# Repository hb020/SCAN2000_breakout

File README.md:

# SCAN2000_breakout

This repository contains the KiCAD and Freecad project files for a breakout panel for for a Keithley SCAN2000-20 replacement card.

It is a specific breakout board in the sense that it holds the (solid-state) relays inside, lowering the overal electrical noise.

It is supposed to be matched with the board from [here](https://github.com/hb020/SCAN2000):

either directly, either via a small mezzanine driver/ESD suppression board that can be found in the [/SCAN2000_driver](/SCAN2000_driver) directory.

That latter board will give a bit more protection against small electrical mishaps, and will allow a load of up to 24 or 35mA per pin (depending on the chip manufacturer), instead of 15mA, allowing extra leds to be driven.

To facilitate plugging/unplugging from the DMM, I also made a small 4 pin connector board for the back of the DMM. See the [/SCAN2000_rearconn](/SCAN2000_rearconn) directory.

# Functionality

The board provides 20 channels:

* 2 banana inputs meant for current measurements. It uses 100 mOhm kelvin shunts, allowing up to 2A. One could go higher with lower shunt values or larger package sizes. Note that the accuracy in the µA range suffers from the noise and leak currents in the SSR. This means that if you want a higher current handling capacity, you will sacrifice low current accuracy. And the reverse of course. There are 2 inputs like it, so you are free to adjust, and you can always use external shunts.
* 8 banana inputs for voltage measurements or 4W resistance measurements.
* 10 pin header inputs for voltage measurements or 4W resistance measurements.

# Calibration

See the [/scan2000_calibrate](/scan2000_calibrate) directory for the determination of the multiplication factors for the voltage to current conversion on channels 1 and 11. Can be done simpler though.

A sample TSP file is [here](breakoutAmps.tsp). You may want to add that to your autoexec script.

# Production

The case chosen is a Hammond 1590QBK. It is just small enough to fit everything required inside, and not be a space hogger on my desk. It machines well, even on my rather low end CNC:

The Freecad files, the GCode, as well as the front stickers, are in the [/freecad](/freecad) directory.
The paint on it is not completely flat, making sticker adhesion a bit more difficult and making milled text not practical.

The grounding of the case is done through a threaded rivet in the case that is connected to the ground screw on the rear of the DMM via the shielding of the OUT cable.

# TODO

* Integrate the mezzanine board in the SCAN2000 board. But then I should also replace the ESD diodes by a real overvoltage protection. The used diodes are effective against some types of ESD, but get damaged easily with DC currents. And hand soldering them isn't easy.
* Find a black 26 pin flat cable header, the white one I got now hurts the eyes.
* Use nicer connectors than the MSTB 5.08 connectors. The OUT/SENSE cables that I used to connect to the DMM are shielded, making them just a bit stiff, so I had to use MSTB 2,5/ 2-STZ-5,08 connectors that have strain relief. It would be better to move to a regular 4 or 5 pin connector.
* Make a 3D printed case for the rearconn connector. I just applied plastic coating to the PCB, not ideal.

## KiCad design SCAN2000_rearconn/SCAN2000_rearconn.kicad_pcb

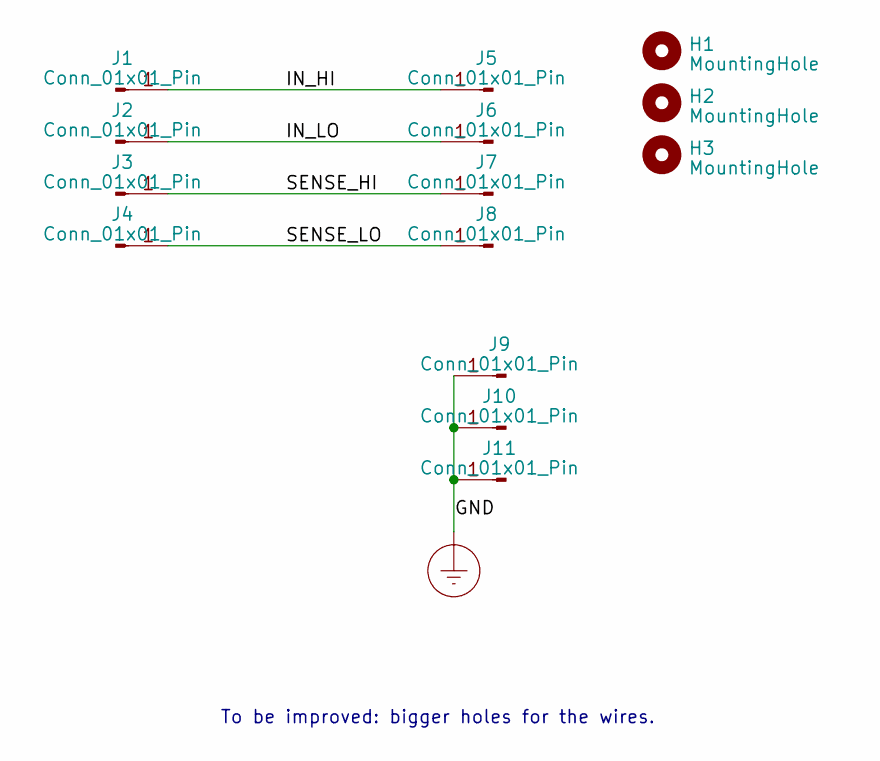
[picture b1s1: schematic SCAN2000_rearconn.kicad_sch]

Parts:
H1, H2, H3: MountingHole; tiewrap_hole
J1, J2, J3, J4: Conn_01x01_Pin; Banana_Jack_1Pin
J5, J6, J7, J8, J9, J10, J11: Conn_01x01_Pin; SolderWire-0.5sqmm_1x01_D0.9mm_OD2.3mm

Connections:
/IN_HI: J1.1, J5.1
/IN_LO: J2.1, J6.1
/SENSE_HI: J3.1, J7.1
/SENSE_LO: J4.1, J8.1
Earth_Protective: J9.1, J10.1, J11.1

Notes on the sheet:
To be improved: bigger holes for the wires.

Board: 2 copper layers, 14 parts (0 on the bottom side), 5 nets, no tracks yet.

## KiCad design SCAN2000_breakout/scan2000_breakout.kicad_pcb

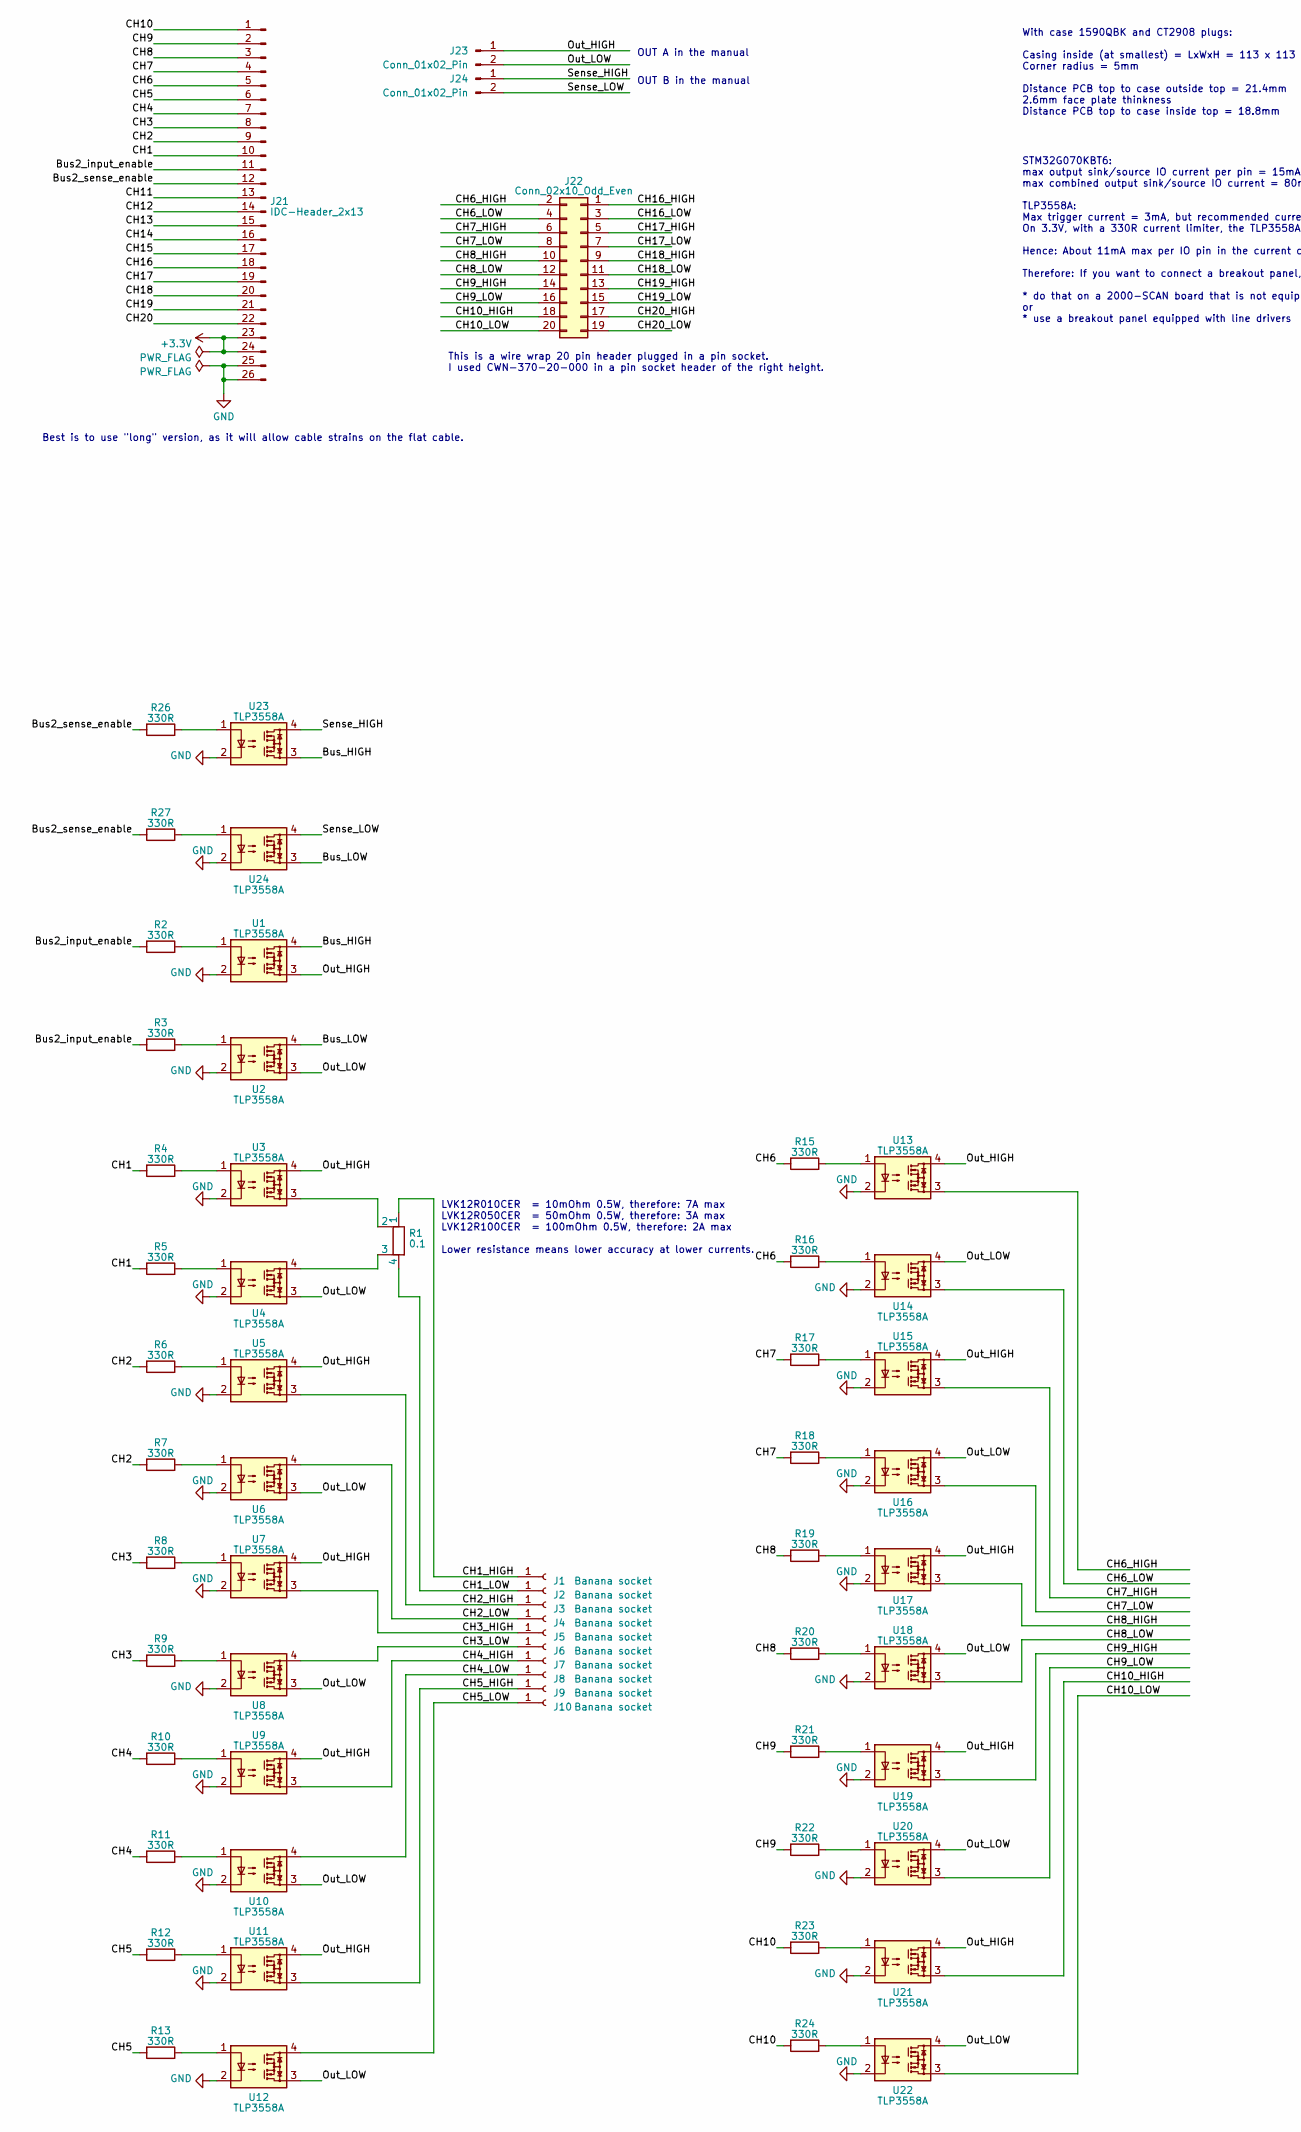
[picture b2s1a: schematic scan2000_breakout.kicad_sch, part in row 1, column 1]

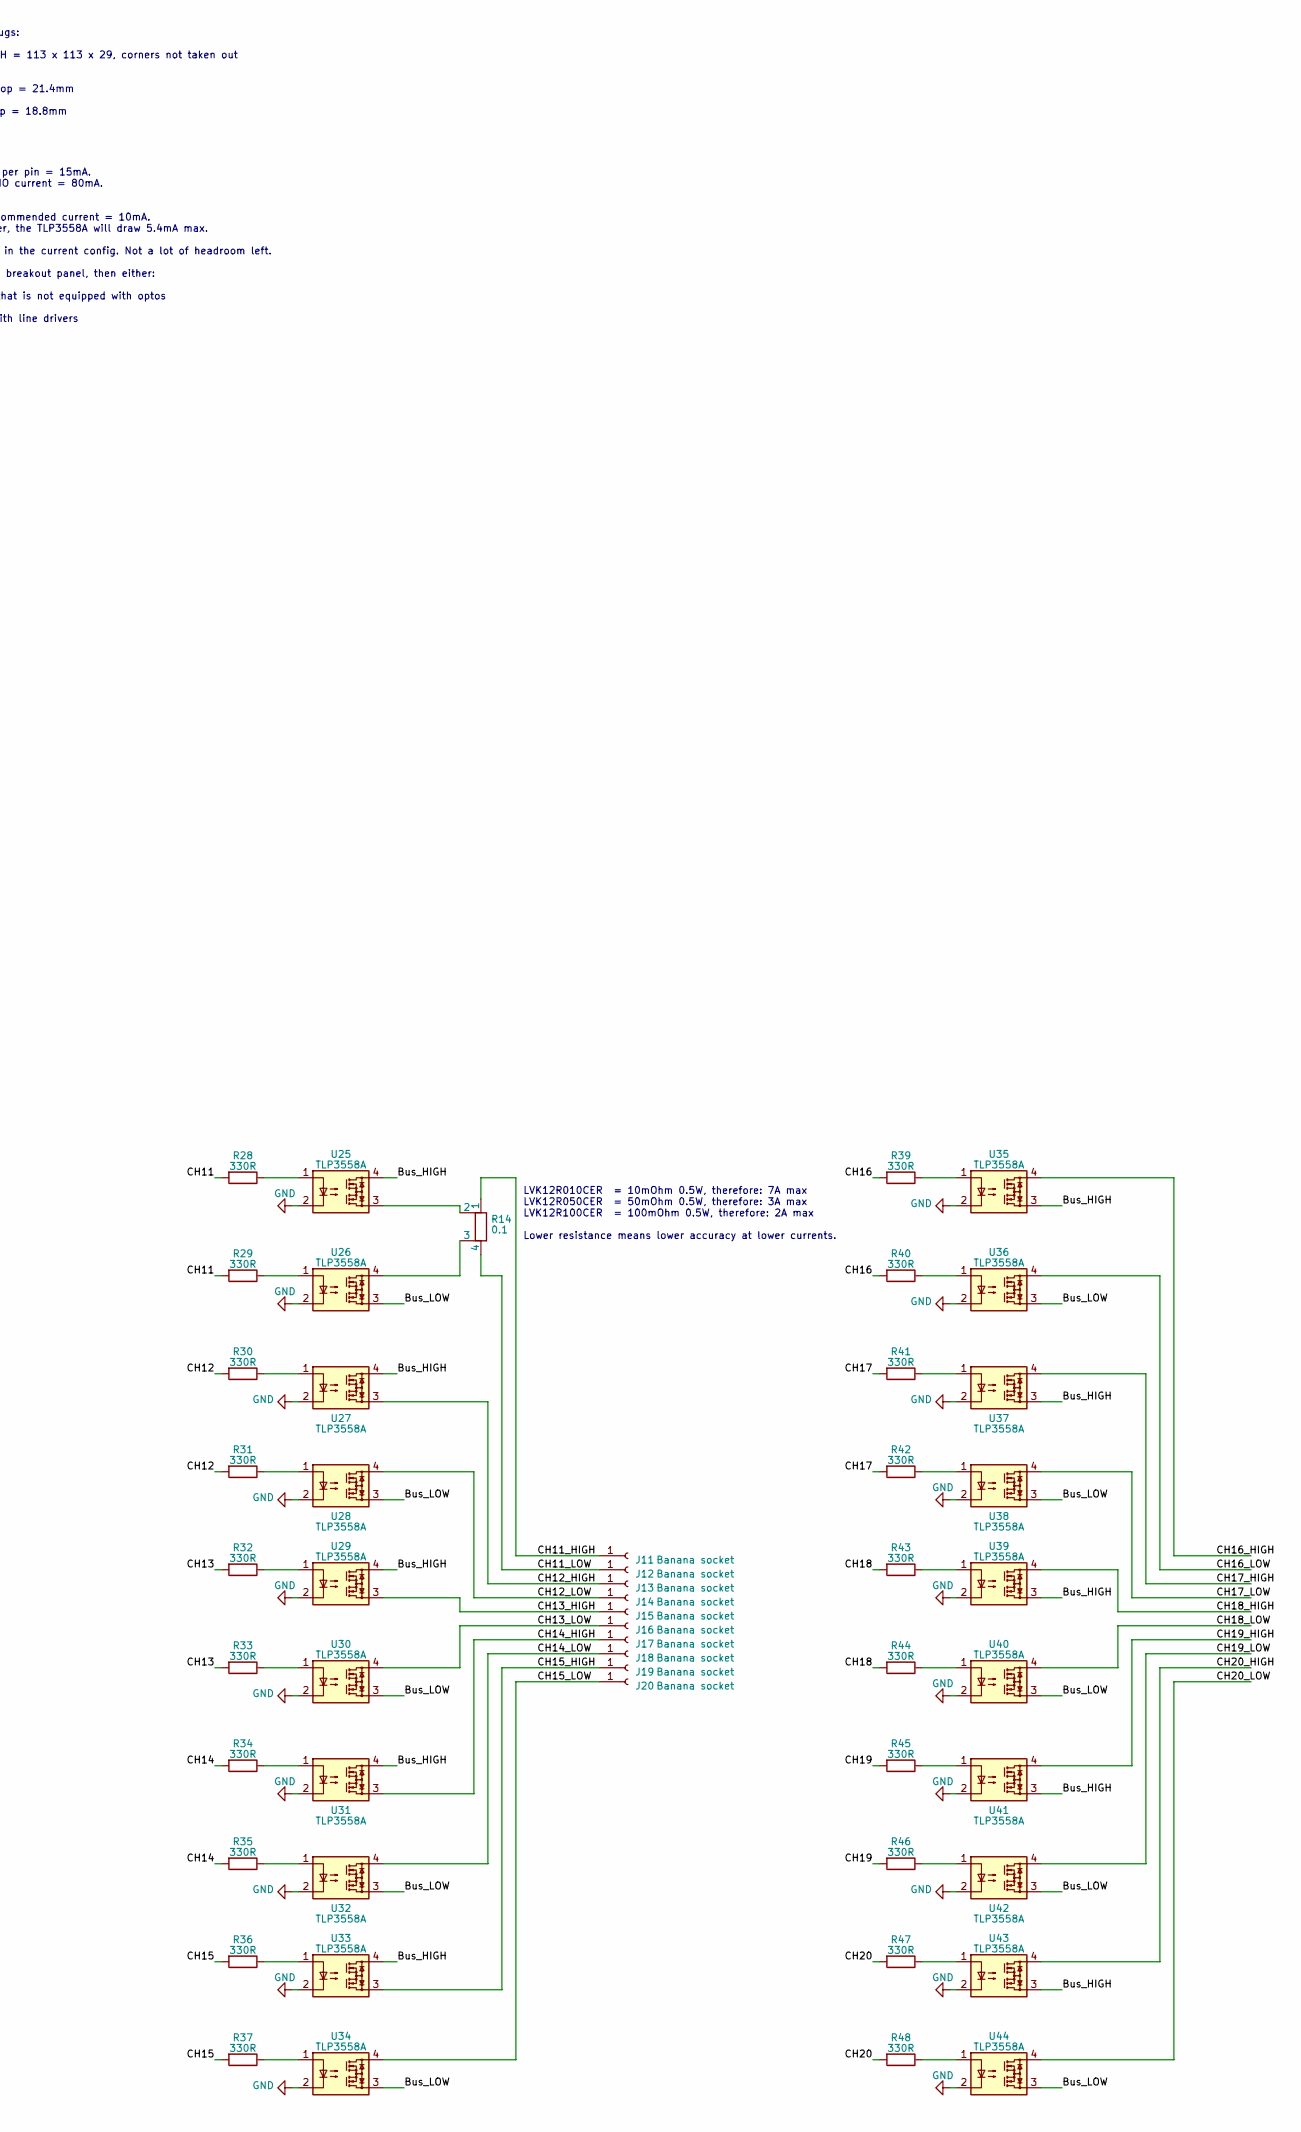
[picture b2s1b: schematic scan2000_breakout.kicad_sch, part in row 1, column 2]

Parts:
J1, J3, J5, J7, J9, J11, J13, J15, J17, J19: Banana socket; CT2908-1
J2, J4, J6, J8, J10, J12, J14, J16, J18, J20: Banana socket; CT2908-0
J21: IDC-Header_2x13; IDC-Header_2x13_P2.54mm_Latch_Horizontal
J22: Conn_02x10_Odd_Even; PinSocket_2x10_P2.54mm_Vertical
J23, J24: Conn_01x02_Pin; PhoenixContact_MSTBA_2,5_2-G-5,08_1x02_P5.08mm_Horizontal
R1, R14: 0.1; R_Shunt_Ohmite_LVK12_ALT2
R2, R3, R4, R5, R6, R7, R8, R9, R10, R11, R12, R13, R15, R16, R17, R18, R19, R20, R21, R22, R23, R24, R26, R27, R28, R29, R30, R31, R32, R33, R34, R35, R36, R37, R39, R40, R41, R42, R43, R44, R45, R46, R47, R48: 330R; R_0603_1608Metric
U1, U2, U3, U4, U5, U6, U7, U8, U9, U10, U11, U12, U13, U14, U15, U16, U17, U18, U19, U20, U21, U22, U23, U24, U25, U26, U27, U28, U29, U30, U31, U32, U33, U34, U35, U36, U37, U38, U39, U40, U41, U42, U43, U44: TLP3558A; DIP-4_W7.62mm

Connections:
+3.3V: J21.23, J21.24
/Bus2_input_enable: J21.11, R2.2, R3.2
/Bus2_sense_enable: J21.12, R26.2, R27.2
/Bus_HIGH: U1.4, U23.3, U25.4, U27.4, U29.4, U31.4, U33.4, U35.3, U37.3, U39.3, U41.3, U43.3
/Bus_LOW: U2.4, U24.3, U26.3, U28.3, U30.3, U32.3, U34.3, U36.3, U38.3, U40.3, U42.3, U44.3
/CH1: J21.10, R4.2, R5.2
/CH1_HIGH: J1.1, R1.1
/CH1_LOW: J2.1, R1.4
/CH2: J21.9, R6.2, R7.2
/CH2_HIGH: J3.1, U5.3
/CH2_LOW: J4.1, U6.4
/CH3: J21.8, R8.2, R9.2
/CH3_HIGH: J5.1, U7.3
/CH3_LOW: J6.1, U8.4
/CH4: J21.7, R10.2, R11.2
/CH4_HIGH: J7.1, U9.3
/CH4_LOW: J8.1, U10.4
/CH5: J21.6, R12.2, R13.2
/CH5_HIGH: J9.1, U11.3
/CH5_LOW: J10.1, U12.4
/CH6: J21.5, R15.2, R16.2
/CH6_HIGH: J22.2, U13.3
/CH6_LOW: J22.4, U14.3
/CH7: J21.4, R17.2, R18.2
/CH7_HIGH: J22.6, U15.3
/CH7_LOW: J22.8, U16.3
/CH8: J21.3, R19.2, R20.2
/CH8_HIGH: J22.10, U17.3
/CH8_LOW: J22.12, U18.3
/CH9: J21.2, R21.2, R22.2
/CH9_HIGH: J22.14, U19.3
/CH9_LOW: J22.16, U20.3
/CH10: J21.1, R23.2, R24.2
/CH10_HIGH: J22.18, U21.3
/CH10_LOW: J22.20, U22.3
/CH11: J21.13, R28.2, R29.2
/CH11_HIGH: J11.1, R14.1
/CH11_LOW: J12.1, R14.4
/CH12: J21.14, R30.2, R31.2
/CH12_HIGH: J13.1, U27.3
/CH12_LOW: J14.1, U28.4
/CH13: J21.15, R32.2, R33.2
/CH13_HIGH: J15.1, U29.3
/CH13_LOW: J16.1, U30.4
/CH14: J21.16, R34.2, R35.2
/CH14_HIGH: J17.1, U31.3
/CH14_LOW: J18.1, U32.4
/CH15: J21.17, R36.2, R37.2
/CH15_HIGH: J19.1, U33.3
/CH15_LOW: J20.1, U34.4
/CH16: J21.18, R39.2, R40.2
/CH16_HIGH: J22.1, U35.4
/CH16_LOW: J22.3, U36.4
/CH17: J21.19, R41.2, R42.2
/CH17_HIGH: J22.5, U37.4
/CH17_LOW: J22.7, U38.4
/CH18: J21.20, R43.2, R44.2
/CH18_HIGH: J22.9, U39.4
/CH18_LOW: J22.11, U40.4
/CH19: J21.21, R45.2, R46.2
/CH19_HIGH: J22.13, U41.4
/CH19_LOW: J22.15, U42.4
/CH20: J21.22, R47.2, R48.2
/CH20_HIGH: J22.17, U43.4
/CH20_LOW: J22.19, U44.4
/Out_HIGH: J23.1, U1.3, U3.4, U5.4, U7.4, U9.4, U11.4, U13.4, U15.4, U17.4, U19.4, U21.4
/Out_LOW: J23.2, U2.3, U4.3, U6.3, U8.3, U10.3, U12.3, U14.4, U16.4, U18.4, U20.4, U22.4
/Sense_HIGH: J24.1, U23.4
/Sense_LOW: J24.2, U24.4
GND: J21.25, J21.26, U1.2, U2.2, U3.2, U4.2, U5.2, U6.2, U7.2, U8.2, U9.2, U10.2, U11.2, U12.2, U13.2, U14.2, U15.2, U16.2, U17.2, U18.2, U19.2, U20.2, U21.2, U22.2, U23.2, U24.2, U25.2, U26.2, U27.2, U28.2, U29.2, U30.2, U31.2, U32.2, U33.2, U34.2, U35.2, U36.2, U37.2, U38.2, U39.2, U40.2, U41.2, U42.2, U43.2, U44.2
unnamed: R1.2, U3.3
unnamed: R1.3, U4.4
unnamed: R2.1, U1.1
unnamed: R3.1, U2.1
unnamed: R4.1, U3.1
unnamed: R5.1, U4.1
unnamed: R6.1, U5.1
unnamed: R7.1, U6.1
unnamed: R8.1, U7.1
unnamed: R9.1, U8.1
unnamed: R10.1, U9.1
unnamed: R11.1, U10.1
unnamed: R12.1, U11.1
unnamed: R13.1, U12.1
unnamed: R14.2, U25.3
unnamed: R14.3, U26.4
unnamed: R15.1, U13.1
unnamed: R16.1, U14.1
unnamed: R17.1, U15.1
unnamed: R18.1, U16.1
unnamed: R19.1, U17.1
unnamed: R20.1, U18.1
unnamed: R21.1, U19.1
unnamed: R22.1, U20.1
unnamed: R23.1, U21.1
unnamed: R24.1, U22.1
unnamed: R26.1, U23.1
unnamed: R27.1, U24.1
unnamed: R28.1, U25.1
unnamed: R29.1, U26.1
unnamed: R30.1, U27.1
unnamed: R31.1, U28.1
unnamed: R32.1, U29.1
unnamed: R33.1, U30.1
unnamed: R34.1, U31.1
unnamed: R35.1, U32.1
unnamed: R36.1, U33.1
unnamed: R37.1, U34.1
unnamed: R39.1, U35.1
unnamed: R40.1, U36.1
unnamed: R41.1, U37.1
unnamed: R42.1, U38.1
unnamed: R43.1, U39.1
unnamed: R44.1, U40.1
unnamed: R45.1, U41.1
unnamed: R46.1, U42.1
unnamed: R47.1, U43.1
unnamed: R48.1, U44.1

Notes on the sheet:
LVK12R010CER = 10mOhm 0.5W, therefore: 7A max LVK12R050CER = 50mOhm 0.5W, therefore: 3A max LVK12R100CER = 100mOhm 0.5W, therefore: 2A max Lower resistance means lower accuracy at lower currents.
Best is to use "long" version, as it will allow cable strains on the flat cable.
OUT B in the manual
STM32G070KBT6: max output sink/source IO current per pin = 15mA. max combined output sink/source IO current = 80mA. TLP3558A: Max trigger current = 3mA, but recommended current = 10mA. On 3.3V, with a 330R current limiter, the TLP3558A will draw 5.4mA max. Hence: About 11mA max per IO pin in the cu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
OUT A in the manual
With case 1590QBK and CT2908 plugs: Casing inside (at smallest) = LxWxH = 113 x 113 x 29, corners not taken out Corner radius = 5mm Distance PCB top to case outside top = 21.4mm 2.6mm face plate thinkness Distance PCB top to case inside top = 18.8mm
This is a wire wrap 20 pin header plugged in a pin socket. I used CWN-370-20-000 in a pin socket header of the right height.

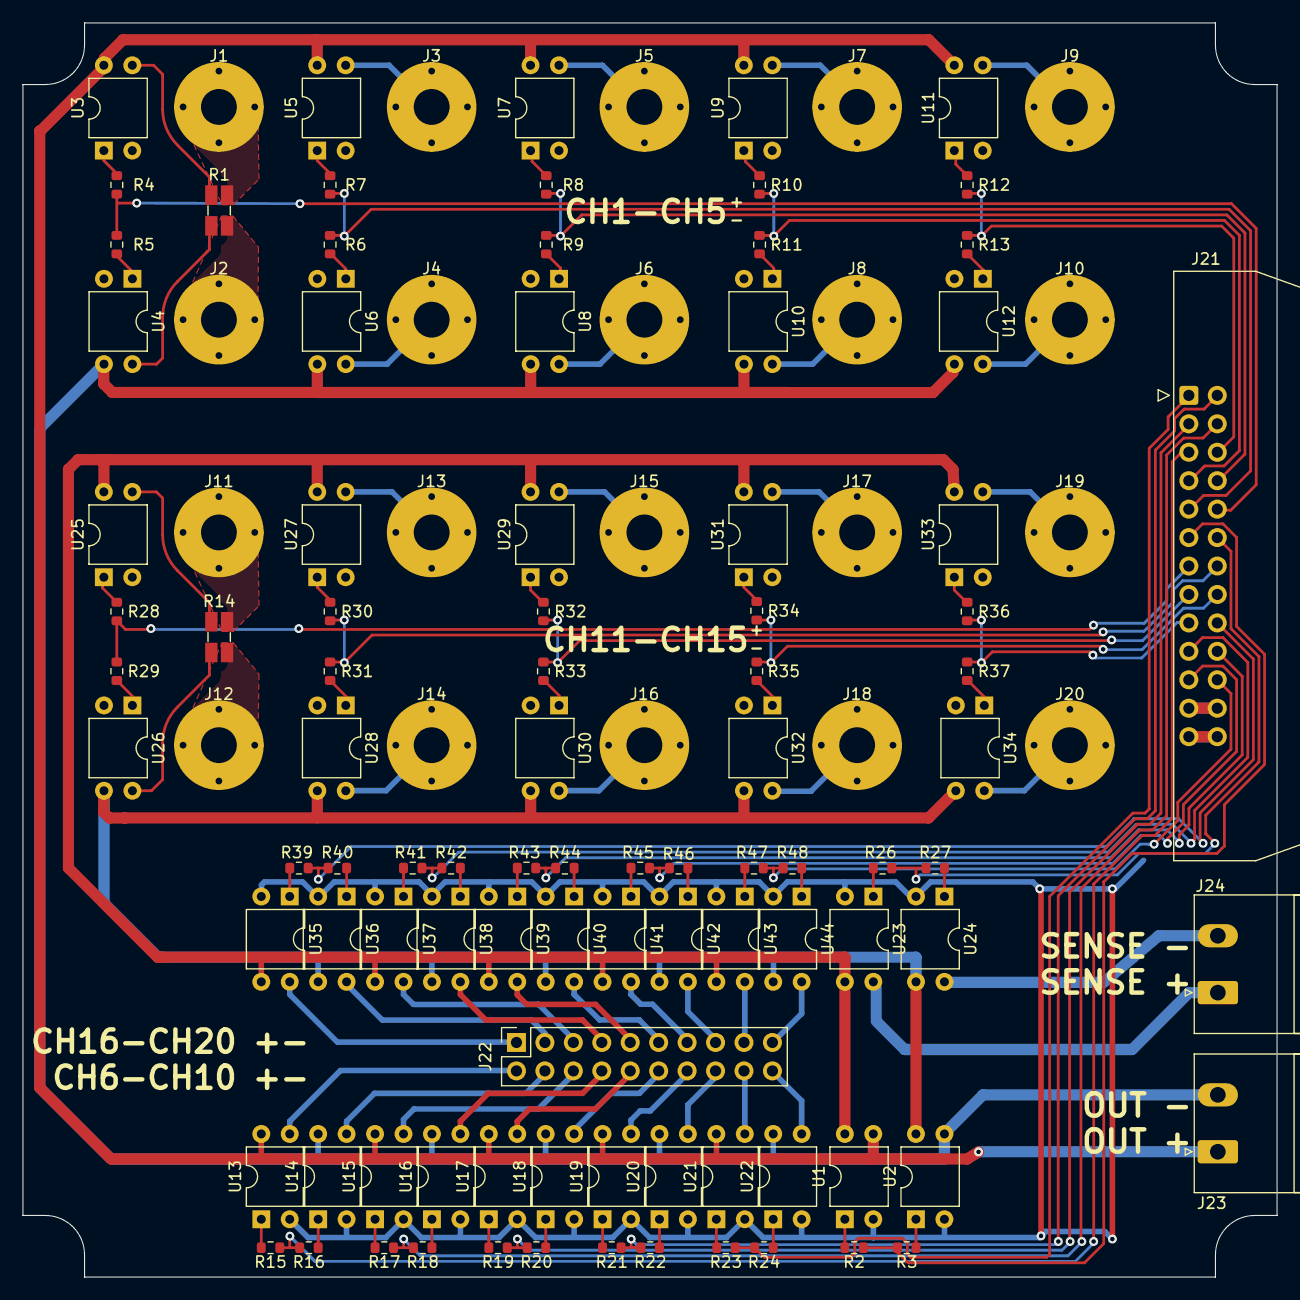
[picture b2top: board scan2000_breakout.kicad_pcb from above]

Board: 2 copper layers, 112.0 x 112.0 mm, 114 parts (0 on the bottom side), 118 nets.

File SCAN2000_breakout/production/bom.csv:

Designator,Footprint,Quantity,Value,LCSC Part #
"J1, J11, J13, J15, J17, J19, J3, J5, J7, J9",CT2908-1,10,Banana socket,
"J10, J12, J14, J16, J18, J2, J20, J4, J6, J8",CT2908-0,10,Banana socket,
J21,IDC-Header_2x13_P2.54mm_Latch_Horizontal,1,Conn_01x26_HIGHin,
J22,PinSocket_2x10_P2.54mm_Vertical,1,Conn_02x10_Odd_Even,
"J23, J24","PhoenixContact_MSTBA_2,5_2-G-5,08_1x02_P5.08mm_Horizontal",2,Conn_01x02_Pin,
"R1, R14",R_Shunt_Ohmite_LVK12_ALT2,2,0.05,
"R10, R11, R12, R13, R15, R16, R17, R18, R19, R2, R20, R21, R22, R23, R24, R26, R27, R28, R29, R3, R30, R31, R32, R33, R34, R35, R36, R37, R39, R4, R40, R41, R42, R43, R44, R45, R46, R47, R48, R5, R6, R7, R8, R9",0603,44,330R,
"U1, U10, U11, U12, U13, U14, U15, U16, U17, U18, U19, U2, U20, U21, U22, U23, U24, U25, U26, U27, U28, U29, U3, U30, U31, U32, U33, U34, U35, U36, U37, U38, U39, U4, U40, U41, U42, U43, U44, U5, U6, U7, U8, U9",DIP-4_W7.62mm,44,TLP3558A,

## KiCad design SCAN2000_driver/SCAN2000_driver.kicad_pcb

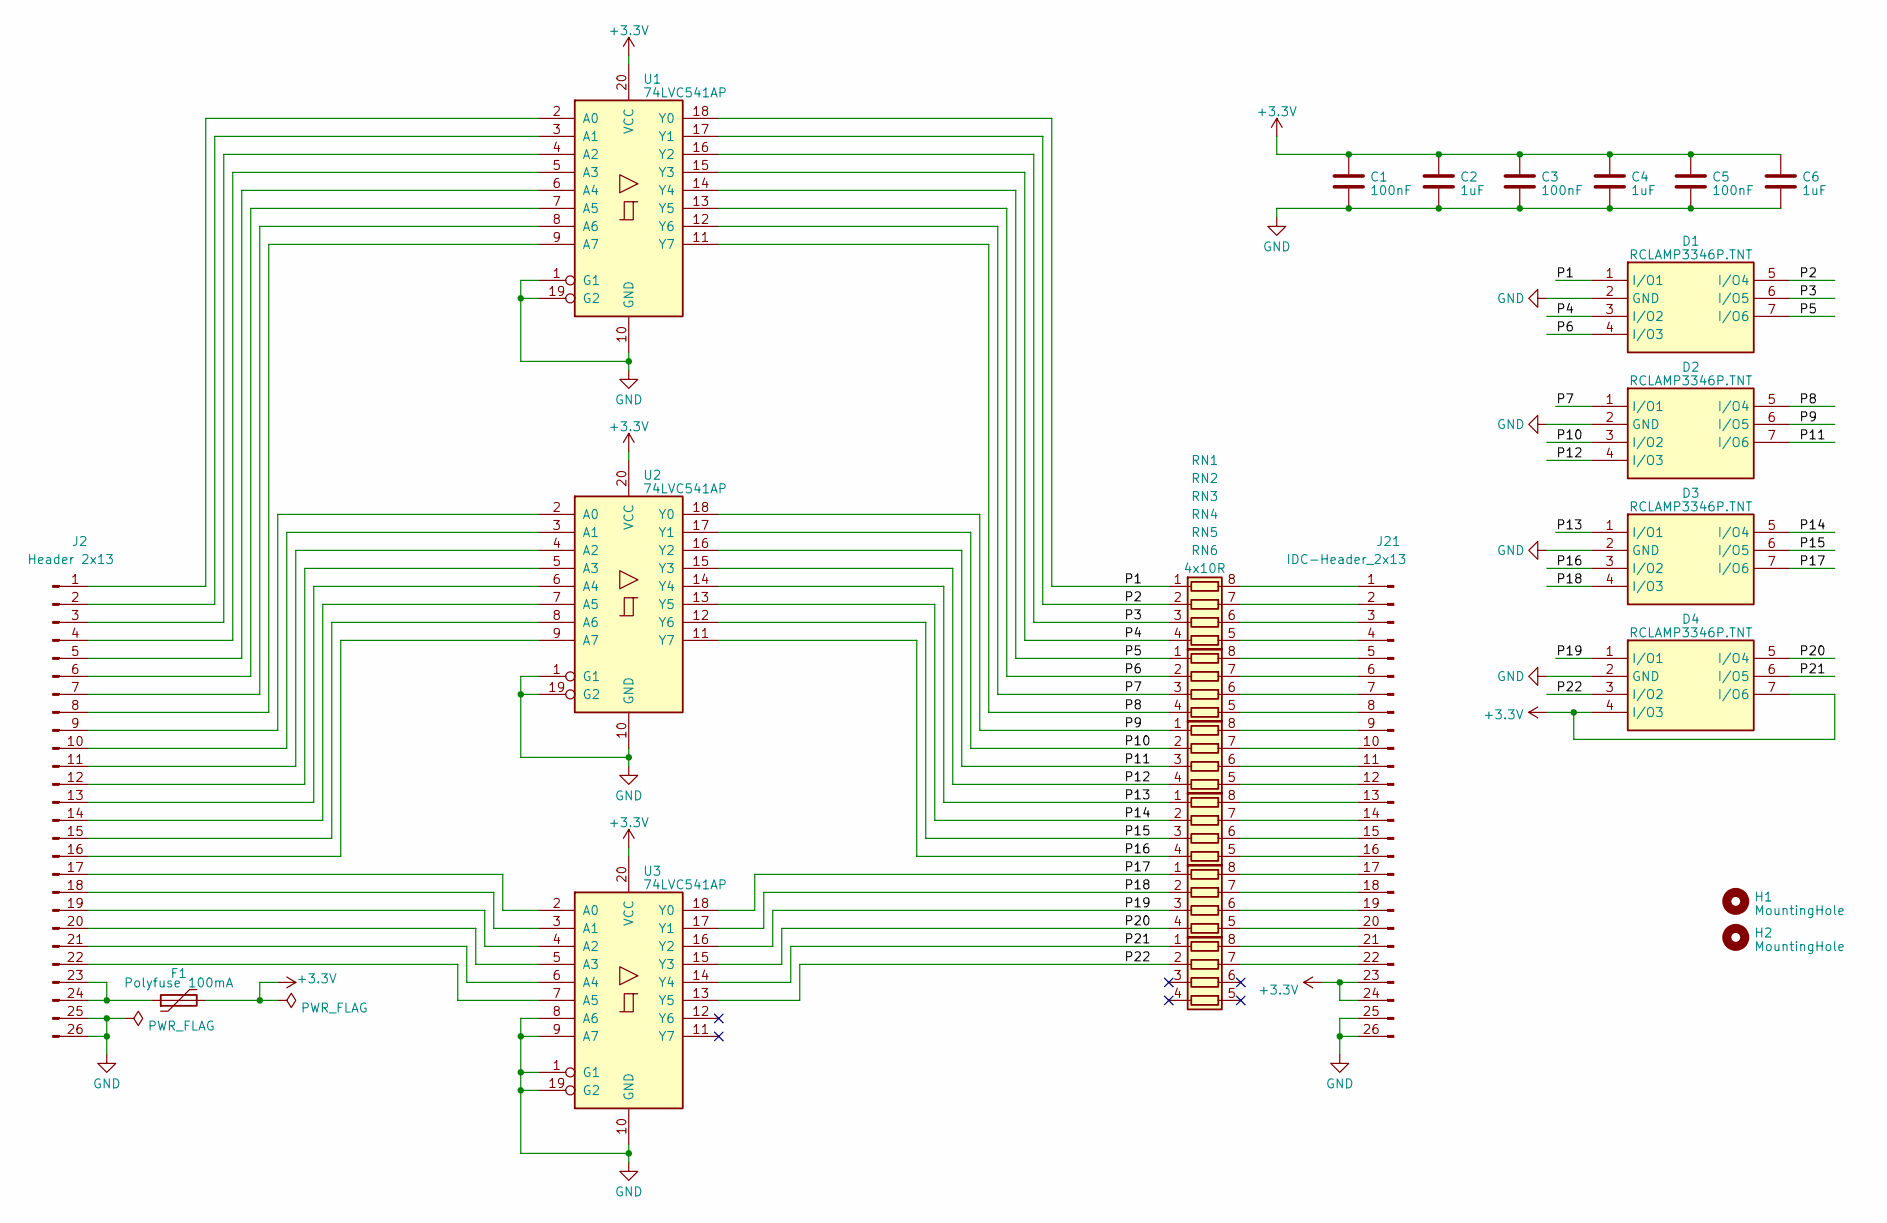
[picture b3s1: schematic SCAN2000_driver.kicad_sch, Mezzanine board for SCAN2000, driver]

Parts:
C1, C3, C5: 100nF; C_0603_1608Metric_Pad1.08x0.95mm_HandSolder
C2, C4, C6: 1uF; C_0805_2012Metric_Pad1.18x1.45mm_HandSolder
D1, D2, D3, D4: RCLAMP3346P.TNT; RCLAMP3346PQTNT; Manufacturer_Part_Number RCLAMP3346P.TNT; Mouser Part Number 947-RCLAMP3346P.TNT
F1: Polyfuse 100mA; R_1206_3216Metric_Pad1.30x1.75mm_HandSolder
H1, H2: MountingHole; MountingHole_3.2mm_M3_DIN965
J2: Header 2x13; PinHeader_2x13_P2.54mm_Vertical
J21: IDC-Header_2x13; IDC-Header_2x13_P2.54mm_Latch_Horizontal
RN1, RN2, RN3, RN4, RN5, RN6: 4x10R; R_Array_Convex_4x0603
U1, U2, U3: 74LVC541AP; TSSOP-20_4.4x6.5mm_P0.65mm

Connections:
+3.3V: C1.1, C2.1, C3.1, C4.1, C5.1, C6.1, D4.4 (I/O3), D4.7 (I/O6), F1.2, U1.20 (VCC), U2.20 (VCC), U3.20 (VCC); also elsewhere on the board
/P1: D1.1 (I/O1), RN1.1 (R1.1), U1.18 (Y0)
/P2: D1.5 (I/O4), RN1.2 (R2.1), U1.17 (Y1)
/P3: D1.6 (I/O5), RN1.3 (R3.1), U1.16 (Y2)
/P4: D1.3 (I/O2), RN1.4 (R4.1), U1.15 (Y3)
/P5: D1.7 (I/O6), RN2.1 (R1.1), U1.14 (Y4)
/P6: D1.4 (I/O3), RN2.2 (R2.1), U1.13 (Y5)
/P7: D2.1 (I/O1), RN2.3 (R3.1), U1.12 (Y6)
/P8: D2.5 (I/O4), RN2.4 (R4.1), U1.11 (Y7)
/P9: D2.6 (I/O5), RN3.1 (R1.1), U2.18 (Y0)
/P10: D2.3 (I/O2), RN3.2 (R2.1), U2.17 (Y1)
/P11: D2.7 (I/O6), RN3.3 (R3.1), U2.16 (Y2)
/P12: D2.4 (I/O3), RN3.4 (R4.1), U2.15 (Y3)
/P13: D3.1 (I/O1), RN4.1 (R1.1), U2.14 (Y4)
/P14: D3.5 (I/O4), RN4.2 (R2.1), U2.13 (Y5)
/P15: D3.6 (I/O5), RN4.3 (R3.1), U2.12 (Y6)
/P16: D3.3 (I/O2), RN4.4 (R4.1), U2.11 (Y7)
/P17: D3.7 (I/O6), RN5.1 (R1.1), U3.18 (Y0)
/P18: D3.4 (I/O3), RN5.2 (R2.1), U3.17 (Y1)
/P19: D4.1 (I/O1), RN5.3 (R3.1), U3.16 (Y2)
/P20: D4.5 (I/O4), RN5.4 (R4.1), U3.15 (Y3)
/P21: D4.6 (I/O5), RN6.1 (R1.1), U3.14 (Y4)
/P22: D4.3 (I/O2), RN6.2 (R2.1), U3.13 (Y5)
GND: C1.2, C2.2, C3.2, C4.2, C5.2, C6.2, D1.2 (GND), D2.2 (GND), D3.2 (GND), D4.2 (GND), J2.25, J2.26, U1.1 (G1), U1.10 (GND), U1.19 (G2), U2.1 (G1), U2.10 (GND), U2.19 (G2), U3.1 (G1), U3.8 (A6), U3.9 (A7), U3.10 (GND), U3.19 (G2); also elsewhere on the board
unnamed 24: RN1.8 (R1.2); also elsewhere on the board
unnamed 25: RN1.7 (R2.2); also elsewhere on the board
unnamed 26: RN1.6 (R3.2); also elsewhere on the board
unnamed 27: RN1.5 (R4.2); also elsewhere on the board
unnamed 28: RN2.8 (R1.2); also elsewhere on the board
unnamed 29: RN2.7 (R2.2); also elsewhere on the board
unnamed 30: RN2.6 (R3.2); also elsewhere on the board
unnamed 31: RN2.5 (R4.2); also elsewhere on the board
unnamed 32: RN3.8 (R1.2); also elsewhere on the board
unnamed 33: RN3.7 (R2.2); also elsewhere on the board
unnamed 34: RN3.6 (R3.2); also elsewhere on the board
unnamed 35: RN3.5 (R4.2); also elsewhere on the board
unnamed 36: RN4.8 (R1.2); also elsewhere on the board
unnamed 37: RN4.7 (R2.2); also elsewhere on the board
unnamed 38: RN4.6 (R3.2); also elsewhere on the board
unnamed 39: RN4.5 (R4.2); also elsewhere on the board
unnamed 40: RN5.8 (R1.2); also elsewhere on the board
unnamed 41: RN5.7 (R2.2); also elsewhere on the board
unnamed 42: RN5.6 (R3.2); also elsewhere on the board
unnamed 43: RN5.5 (R4.2); also elsewhere on the board
unnamed 44: RN6.8 (R1.2); also elsewhere on the board
unnamed 45: RN6.7 (R2.2); also elsewhere on the board
unnamed: J2.1, U1.2 (A0)
unnamed: J2.2, U1.3 (A1)
unnamed: J2.3, U1.4 (A2)
unnamed: J2.4, U1.5 (A3)
unnamed: J2.5, U1.6 (A4)
unnamed: J2.6, U1.7 (A5)
unnamed: J2.7, U1.8 (A6)
unnamed: J2.8, U1.9 (A7)
unnamed: J2.9, U2.2 (A0)
unnamed: J2.10, U2.3 (A1)
unnamed: J2.11, U2.4 (A2)
unnamed: J2.12, U2.5 (A3)
unnamed: J2.13, U2.6 (A4)
unnamed: J2.14, U2.7 (A5)
unnamed: J2.15, U2.8 (A6)
unnamed: J2.16, U2.9 (A7)
unnamed: J2.17, U3.2 (A0)
unnamed: J2.18, U3.3 (A1)
unnamed: J2.19, U3.4 (A2)
unnamed: J2.20, U3.5 (A3)
unnamed: J2.21, U3.6 (A4)
unnamed: J2.22, U3.7 (A5)
unnamed: F1.1, J2.23, J2.24

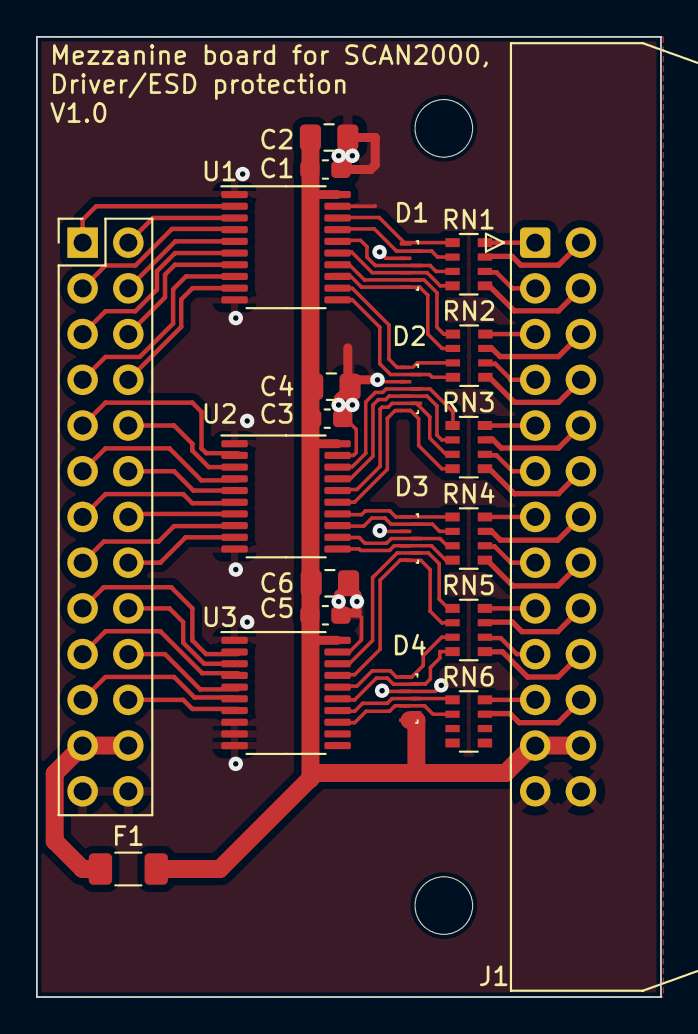
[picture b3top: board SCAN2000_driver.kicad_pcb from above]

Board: 2 copper layers, 34.7 x 53.3 mm, 24 parts (0 on the bottom side), 69 nets.

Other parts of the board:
J1: IDC-Header_2x13; IDC-Header_2x13_P2.54mm_Latch_Horizontal

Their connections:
+3.3V: J1.23, J1.24; also elsewhere on the board
GND: J1.25, J1.26; also elsewhere on the board
unnamed 24: J1.1; also elsewhere on the board
unnamed 25: J1.2; also elsewhere on the board
unnamed 26: J1.3; also elsewhere on the board
unnamed 27: J1.4; also elsewhere on the board
unnamed 28: J1.5; also elsewhere on the board
unnamed 29: J1.6; also elsewhere on the board
unnamed 30: J1.7; also elsewhere on the board
unnamed 31: J1.8; also elsewhere on the board
unnamed 32: J1.9; also elsewhere on the board
unnamed 33: J1.10; also elsewhere on the board
unnamed 34: J1.11; also elsewhere on the board
unnamed 35: J1.12; also elsewhere on the board
unnamed 36: J1.13; also elsewhere on the board
unnamed 37: J1.14; also elsewhere on the board
unnamed 38: J1.15; also elsewhere on the board
unnamed 39: J1.16; also elsewhere on the board
unnamed 40: J1.17; also elsewhere on the board
unnamed 41: J1.18; also elsewhere on the board
unnamed 42: J1.19; also elsewhere on the board
unnamed 43: J1.20; also elsewhere on the board
unnamed 44: J1.21; also elsewhere on the board
unnamed 45: J1.22; also elsewhere on the board

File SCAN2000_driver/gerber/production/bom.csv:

Designator,Footprint,Quantity,Value,LCSC Part #
"C1, C3, C5",0603,3,100nF,
"C2, C4, C6",0805,3,1uF,
"D1, D2, D3, D4",RCLAMP3346PQTNT,4,RCLAMP3346P.TNT,
F1,1206,1,Polyfuse 100mA,
"H1, H2",MountingHole_3.2mm_M3_DIN965,2,MountingHole,
J1,IDC-Header_2x13_P2.54mm_Latch_Horizontal,1,IDC-Header_2x13,
J2,PinHeader_2x13_P2.54mm_Vertical,1,Header 2x13,
"RN1, RN2, RN3, RN4, RN5, RN6",R_Array_Convex_4x0603,6,4x10R,
"U1, U2, U3",TSSOP-20_4.4x6.5mm_P0.65mm,3,74LVC541AP,

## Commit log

2023-06-04 First content commit
2023-06-06 added mezzanine board
2023-06-07 better doc
2023-06-07 layout problem
2023-06-18 small silkscreen change
2023-06-28 Updates after fabrication
2023-06-28 text clarification
2023-06-29 added calibration script
2023-06-29 Explanation of calibration
2023-06-29 grammar oops
2023-06-30 better testing
2023-07-01 grammar
2023-07-01 oops in error checker
2023-08-10 WIP on better calibration
2023-08-11 test script for SCPI based trigger sync
2023-08-11 better measurement via trigger sync
2023-08-11 fitting done via solver
2023-08-12 added TSP file
2024-04-02 added better script
